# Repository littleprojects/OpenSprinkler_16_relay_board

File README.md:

# OpenSprinkler_16_relay_board
16 relay extention board for BBB with OpenSprinkler

OpenSprinkler 16 Relay board

To control up 16 relays from a BeagleBoardBlack.
With 5V power supply.
And Rain Sensor input.

Send the *.brd to www.platinenbelichter.de. 

He can make you 4 PCB for under 30€.

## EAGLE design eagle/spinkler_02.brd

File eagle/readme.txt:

OpenSprinkler 16 Relay board

To control up 16 relays from a BeagleBoardBlack.
With 5V power supply.
And Rain Sensor input.

Send the *.brd to www.platinenbelichter.de. 

He can make you 4 PCB for under 30.

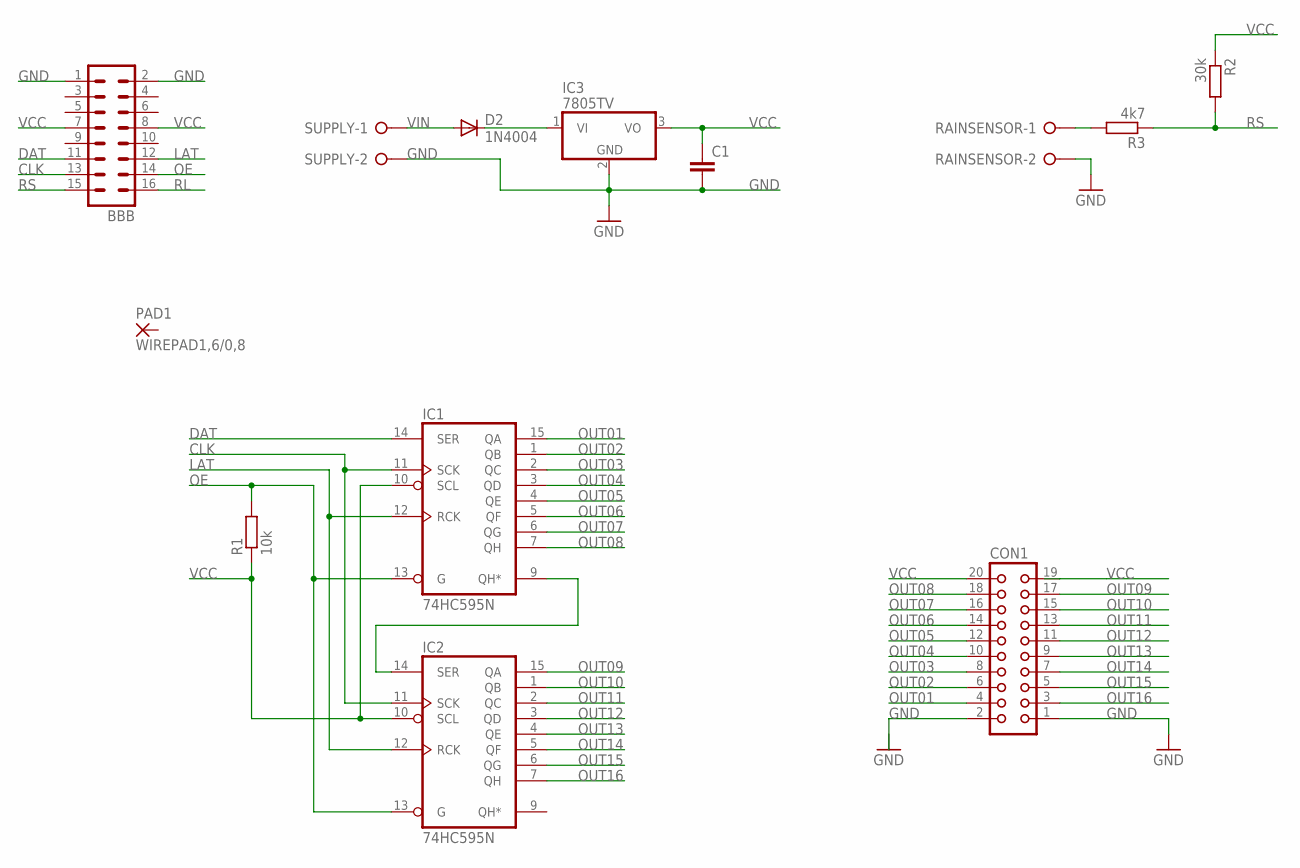
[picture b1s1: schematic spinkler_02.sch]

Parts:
BBB: MA08-2
C1: C-EU050-025X075; C050-025X075
CON1: CON20
D2: 1N4004; DO41-10
IC1, IC2: 74HC595N; DIL16
IC3: 7805TV; TO220V
PAD1: WIREPAD1,6/0,8; 1,6/0,8
R1: 10k; 0207/10
R2: 30k; 0207/10
R3: 4k7; 0207/10
RAINSENSOR: W237-02P; W237-132
SUPPLY: W237-02P; W237-132

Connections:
CLK: BBB.13, IC1.11 (SCK), IC2.11 (SCK)
DAT: BBB.11, IC1.14 (SER)
GND: BBB.1, BBB.2, C1.2, CON1.1, CON1.2, IC1.8 (GND), IC2.8 (GND), IC3.2 (GND), RAINSENSOR.2, SUPPLY.2
LAT: BBB.12, IC1.12 (RCK), IC2.12 (RCK)
unnamed: R3.2, RAINSENSOR.1
unnamed: D2.C, IC3.1 (VI)
unnamed: IC1.9 (QH*), IC2.14 (SER)
OE: BBB.14, IC1.13 (G), IC2.13 (G), R1.2
OUT01: CON1.4, IC1.15 (QA)
OUT02: CON1.6, IC1.1 (QB)
OUT03: CON1.8, IC1.2 (QC)
OUT04: CON1.10, IC1.3 (QD)
OUT05: CON1.12, IC1.4 (QE)
OUT06: CON1.14, IC1.5 (QF)
OUT07: CON1.16, IC1.6 (QG)
OUT08: CON1.18, IC1.7 (QH)
OUT09: CON1.17, IC2.15 (QA)
OUT10: CON1.15, IC2.1 (QB)
OUT11: CON1.13, IC2.2 (QC)
OUT12: CON1.11, IC2.3 (QD)
OUT13: CON1.9, IC2.4 (QE)
OUT14: CON1.7, IC2.5 (QF)
OUT15: CON1.5, IC2.6 (QG)
OUT16: CON1.3, IC2.7 (QH)
RL: BBB.16
RS: BBB.15, R2.2, R3.1
VCC: BBB.7, BBB.8, C1.1, CON1.19, CON1.20, IC1.10 (SCL), IC1.16 (VCC), IC2.10 (SCL), IC2.16 (VCC), IC3.3 (VO), R1.1, R2.1
VIN: D2.A, SUPPLY.1

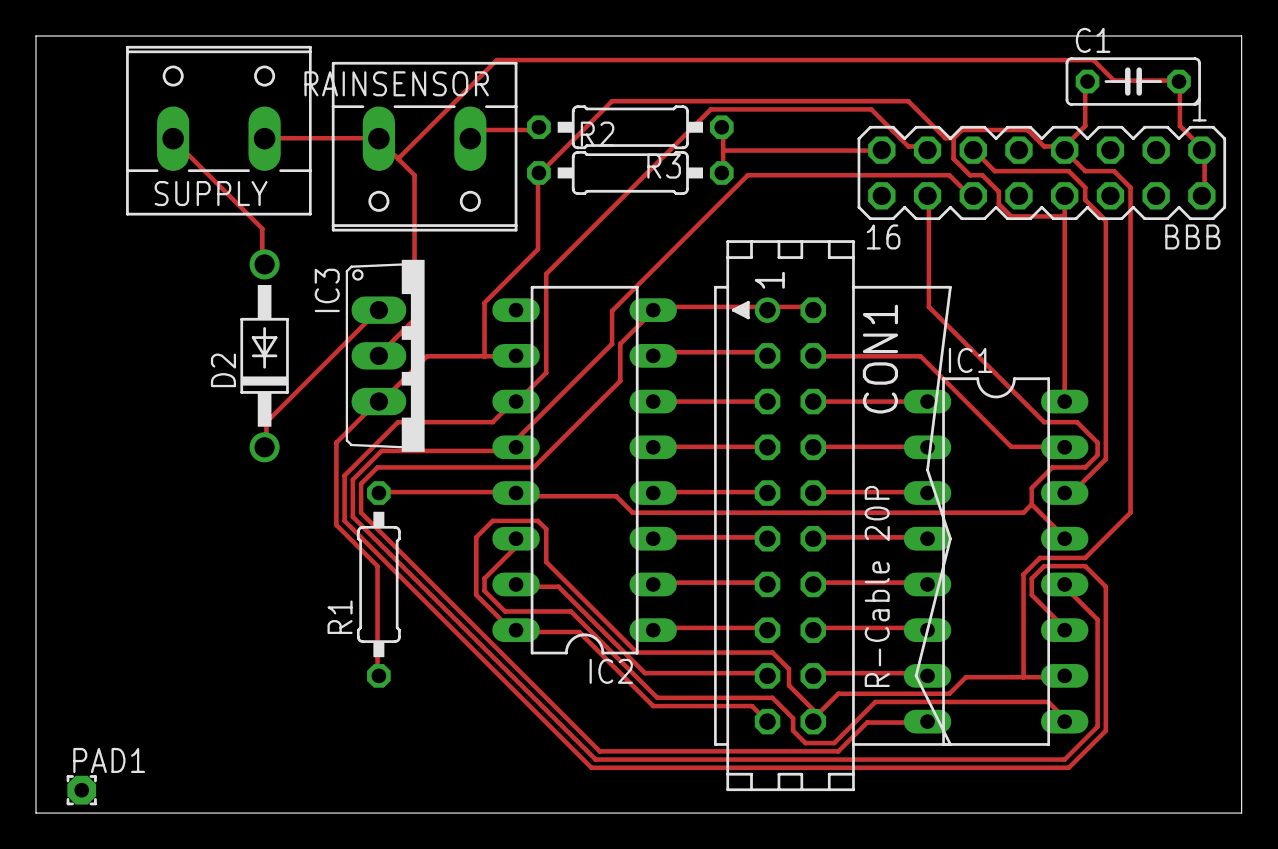
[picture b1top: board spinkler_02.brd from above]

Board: 2 copper layers, 67.0 x 43.2 mm, 13 parts (0 on the bottom side), 27 nets.

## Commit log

2015-08-11 :boom::camel: Added .gitattributes & .gitignore files
2015-08-11 add files
